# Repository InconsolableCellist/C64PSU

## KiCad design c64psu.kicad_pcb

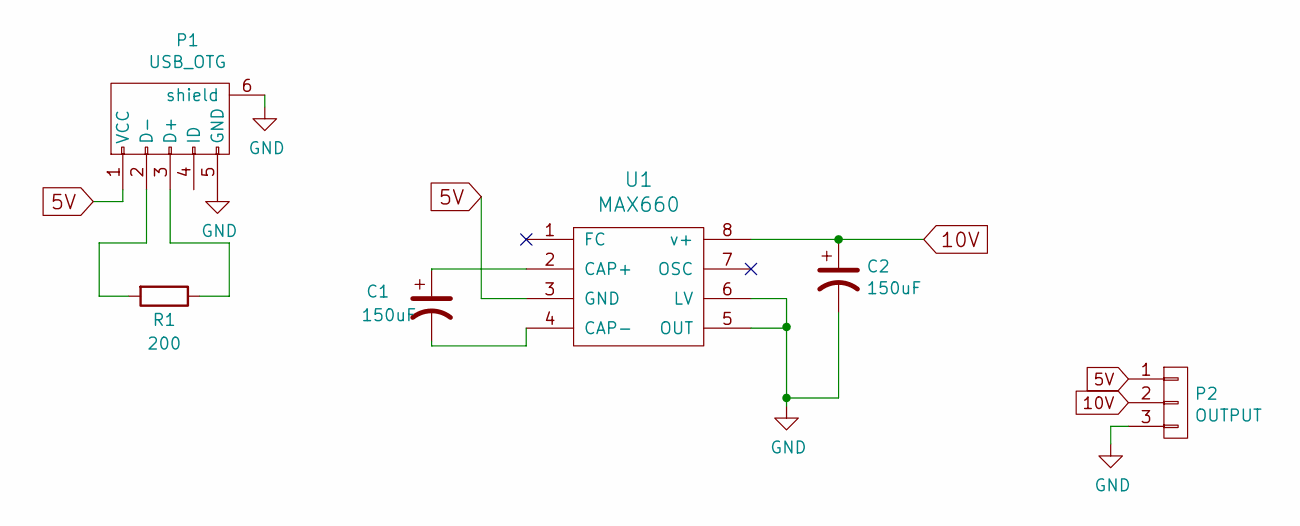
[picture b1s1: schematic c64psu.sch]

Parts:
C1, C2: 150uF; C_Radial_D8_L11.5_P3.5
P1: USB_OTG; USB_Micro-B
P2: OUTPUT; Pin_Header_Straight_1x03_Pitch2.54mm
R1: 200; R_0805
U1: MAX660; SOIC-8_3.9x4.9mm_Pitch1.27mm

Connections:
5V: P1.1 (VCC), P2.1, U1.3 (GND)
10V: C2.1, P2.2, U1.8 (v+)
GND: C2.2, P1.5 (GND), P1.6 (shield), P2.3, U1.5 (OUT), U1.6 (LV)
unnamed: C1.1, U1.2 (CAP+)
unnamed: C1.2, U1.4 (CAP-)
unnamed: P1.2 (D-), R1.2
unnamed: P1.3 (D+), R1.1

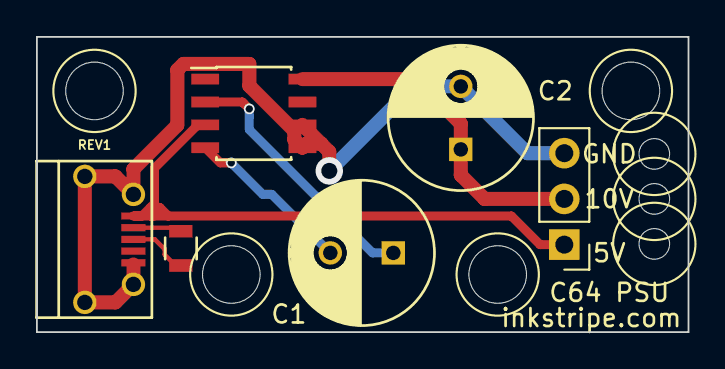
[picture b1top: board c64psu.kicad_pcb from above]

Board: 2 copper layers, 36.2 x 16.4 mm, 6 parts (0 on the bottom side), 7 nets.

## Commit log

2022-03-10 Initial check-in
2022-03-10 Adding case files and README
